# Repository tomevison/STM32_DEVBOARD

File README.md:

# STM32_DEVBOARD
Development board for STM32 microcontroller

Board features a STM32F401RCT6 MCU with a number of peripherals.
- Temperature Humidity Pressure Sensor (Bosch BME280)
- Triple Axis Accelerometer (ST LIS2DW12)
- Tactile Button
- User LED
- USB-C COM Port
- 4-30 VDC input range

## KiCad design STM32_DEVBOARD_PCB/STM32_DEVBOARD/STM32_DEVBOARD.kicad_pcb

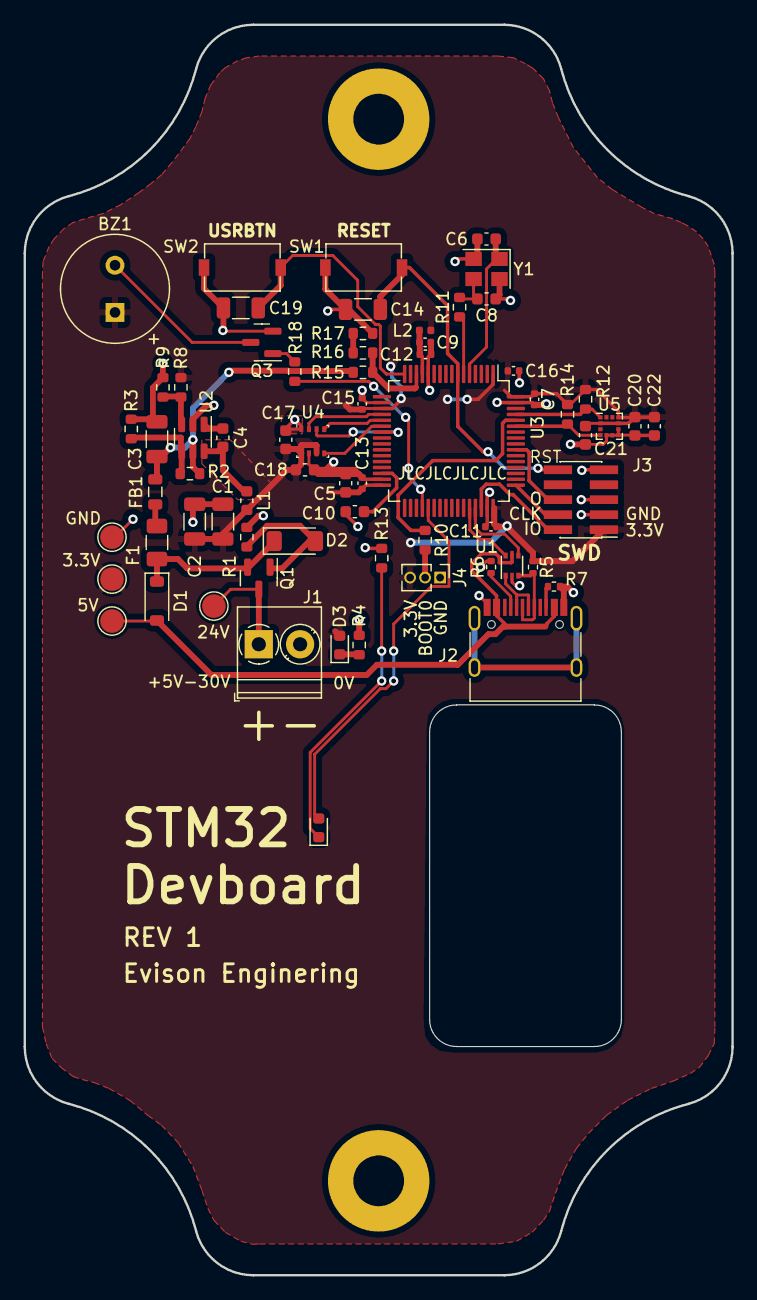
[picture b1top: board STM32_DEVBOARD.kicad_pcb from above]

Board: 2 copper layers, 60.0 x 106.0 mm, 69 parts (0 on the bottom side), 44 nets.

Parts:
BZ1: Buzzer; MagneticBuzzer_CUI_CST-931RP-A
C1, C2, C3: 10u; C_1206_3216Metric
C4: 10n; C_0603_1608Metric
C5, C10: 4u7; C_0603_1608Metric
C6, C8: 10p; C_0603_1608Metric
C7, C11, C13, C15, C16: 100n; C_0402_1005Metric
C9: 1u; C_0402_1005Metric
C12: 10n; C_0402_1005Metric
C14, C19: 0u1; C_1206_3216Metric
C17, C18, C20, C21: 100n; C_0603_1608Metric
C22: 10u; C_0603_1608Metric
D1: B5819W; D_SOD-123
D2: ZMM5V6-M; D_MiniMELF
D3, D4: GRN; LED_0603_1608Metric
F1: 250mA; Fuse_1206_3216Metric
FB1: 600 @ 600MHz; L_0805_2012Metric
H1, H2: MountingHole; MountingHole_4.3mm_M4_Pad
J1: Screw_Terminal_01x02; TerminalBlock_Phoenix_PT-1,5-2-3.5-H_1x02_P3.50mm_Horizontal
J2: USB_C_Receptacle_USB2.0; USB_C_Receptacle_HRO_TYPE-C-31-M-12
J3: SWD; PinHeader_2x05_P1.27mm_Vertical_SMD
J4: Conn_01x03_Pin; PinHeader_1x03_P1.27mm_Vertical
L1: 4.7u; L_0603_1608Metric
L2: 39n; L_0402_1005Metric
Q1: AO3401A; SOT-23
Q3: MMBT3904; SOT-23
R1, R2: 100k; R_0603_1608Metric
R3: 68k; R_0603_1608Metric
R4, R11, R13: R47; R_0603_1608Metric
R5: 1k5; R_0402_1005Metric
R6, R7: 5k1; R_0402_1005Metric
R8: 30k; R_0603_1608Metric
R9, R10, R12, R14, R17: 10k; R_0603_1608Metric
R15: 220k; R_0603_1608Metric
R16: 22k; R_0603_1608Metric
R18: 1k; R_0603_1608Metric
SW1: BTN_RSET; SW_Tactile_SPST_NO_Straight_CK_PTS636-SK25J-SMTR-LFS
SW2: BTN1; SW_Tactile_SPST_NO_Straight_CK_PTS636-SK25J-SMTR-LFS
TP1: GND; TestPoint_Pad_D2.0mm
TP2: 3.3V; TestPoint_Pad_D2.0mm
TP3: 5V; TestPoint_Pad_D2.0mm
TP4: 24V; TestPoint_Pad_D2.0mm
U1: USBLC6-2P6; SOT-666
U2: TPMP2359DJ; SOT-23-6
U3: STM32F401RCTx; LQFP-64_10x10mm_P0.5mm
U4: BME280; Bosch_LGA-8_2.5x2.5mm_P0.65mm_ClockwisePinNumbering
U5: LIS2DW12; LGA-12_2x2mm_P0.5mm
Y1: 16MHz; Crystal_SMD_3225-4Pin_3.2x2.5mm

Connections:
+3.3V: BZ1.1 (-), C1.1, C2.1, C5.1, C7.1, C11.1, C13.1, C15.1, C16.1, C17.1, C18.1, C20.1, C21.1, C22.1, D3.2 (A), J3.1, J4.3, L1.2, L2.1, R5.1, R8.1, R12.1, R14.1, TP2.1, U3.1 (VBAT), U3.19 (VDD), U3.32 (VDD), U3.48 (VDD), U3.64 (VDD), U4.6 (VDDIO), U4.8 (VDD), U5.2 (~CS), U5.9 (Vdd), U5.10 (Vdd_IO)
+3.3VA: C9.1, C12.1, L2.2, U3.13 (VREF+)
+5V: D1.2 (A), J2.A4 (VBUS), J2.A9 (VBUS), J2.B4 (VBUS), J2.B9 (VBUS), TP3.1, U1.5 (VBUS)
+24V: J1.1, Q1.3 (D), TP4.1
BOOT0: R10.2, U3.60 (BOOT0)
BTN1: C19.1, SW2.2, U3.16 (PA2)
BUCK_BST: C4.2, U2.1 (BST)
BUCK_EN: R2.2, R3.1, U2.4 (EN)
BUCK_FB: R8.2, R9.1, U2.3 (FB)
BUCK_IN: C3.1, FB1.2, R2.1, R15.2, U2.5 (IN)
BUCK_SW: C4.1, L1.1, U2.6 (SW)
BUZZ: R18.2, U3.36 (PB15)
GND: C1.2, C2.2, C3.2, C5.2, C6.2, C7.2, C8.2, C9.2, C10.2, C11.2, C12.2, C13.2, C14.2, C15.2, C16.2, C17.2, C18.2, C19.2, C20.2, C21.2, C22.2, J1.2, J2.A1 (GND), J2.A12 (GND), J2.B1 (GND), J2.B12 (GND), J3.3, J3.5, J3.9, J4.1, Q3.2 (E), R1.2, R3.2, R4.1, R6.2, R7.2, R9.2, R13.1, R17.1, SW1.1, SW2.1, TP1.1, U1.2 (GND), U2.2 (GND), U3.12 (VSSA), U3.18 (VSS), U3.31 (VSS), U3.47 (VSS), U3.63 (VSS), U4.1 (GND), U4.7 (GND), U5.5 (RES), U5.6 (GND), U5.7 (GND), U5.8 (GND), Y1.2, Y1.4
I2C1_SCL: R12.2, U3.61 (PB8), U5.1 (SCL/SPC)
I2C1_SDA: R14.2, U3.59 (PB7), U5.4 (SDA/SDI)
LED: D4.2 (A), U3.37 (PC6)
NRST: C14.1, J3.10, SW1.2, U3.7 (NRST)
unnamed: BZ1.2 (+), Q3.3 (C)
unnamed: C8.1, R11.2, Y1.3
unnamed: D1.1 (K), D2.1 (K), F1.2, Q1.2 (S)
unnamed: D2.2 (A), Q1.1 (G), R1.1
unnamed: D3.1 (K), R4.2
unnamed: D4.1 (K), R13.2
unnamed: F1.1, FB1.1
unnamed: J4.2, R10.1
unnamed: Q3.1 (B), R18.1
unnamed: R16.1, R17.2
unnamed: C10.1, U3.30 (VCAP1)
RCC_OSC_IN: C6.1, U3.5 (PH0), Y1.1
RCC_OSC_OUT: R11.1, U3.6 (PH1)
SPI1_CSB: U3.20 (PA4), U4.2 (CSB)
SPI1_MISO: U3.22 (PA6), U4.5 (SDO)
SPI1_MOSI: U3.23 (PA7), U4.3 (SDI)
SPI1_SCK: U3.21 (PA5), U4.4 (SCK)
SWCLK: J3.4, U3.49 (PA14)
SWDIO: J3.2, U3.46 (PA13)
SWO: J3.6, U3.55 (PB3)
USB_CONN_CC1: J2.A5 (CC1), R6.1
USB_CONN_CC2: J2.B5 (CC2), R7.1
USB_CONN_D+: J2.A6 (D+), J2.B6 (D+), R5.2, U1.3 (I/O2)
USB_CONN_D-: J2.A7 (D-), J2.B7 (D-), U1.1 (I/O1)
USB_OTG_FS_DN: U1.6 (I/O1), U3.44 (PA11)
USB_OTG_FS_DP: U1.4 (I/O2), U3.45 (PA12)
VMEAS: R15.1, R16.2, U3.14 (PA0)

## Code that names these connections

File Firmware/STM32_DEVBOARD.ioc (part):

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Mcu.Name=STM32F401R(B-C)Tx
Mcu.Package=LQFP64
Mcu.UserName=STM32F401RCTx
PA0-WKUP.GPIOParameters=GPIO_Label
PA0-WKUP.GPIO_Label=VMEAS
PA0-WKUP.Signal=ADCx_IN0
PA11.Mode=Device_Only
PA11.Signal=USB_OTG_FS_DM
PA12.Mode=Device_Only
PA12.Signal=USB_OTG_FS_DP
PA13.Mode=Trace_Asynchronous_SW
PA13.Signal=SYS_JTMS-SWDIO
PA14.Mode=Trace_Asynchronous_SW
PA14.Signal=SYS_JTCK-SWCLK
PA2.GPIOParameters=GPIO_PuPd,GPIO_Label
PA2.GPIO_Label=BTN1
PA2.GPIO_PuPd=GPIO_PULLUP
PA2.Signal=GPIO_Input
PA4.GPIOParameters=GPIO_Label
PA4.GPIO_Label=SPI1_CSB
PA4.Signal=GPIO_Output
PA5.Mode=Full_Duplex_Master
PA5.Signal=SPI1_SCK
PA6.Mode=Full_Duplex_Master
PA6.Signal=SPI1_MISO
PA7.Mode=Full_Duplex_Master
PA7.Signal=SPI1_MOSI
PB15.Mode=PWM Generation3 CH3N
PB15.Signal=TIM1_CH3N
PB3.Mode=Trace_Asynchronous_SW
PB3.Signal=SYS_JTDO-SWO
PB7.Mode=I2C
PB7.Signal=I2C1_SDA
PB8.Mode=I2C
PB8.Signal=I2C1_SCL
PC6.GPIOParameters=GPIO_Label
PC6.GPIO_Label=LED
PC6.Signal=GPIO_Output
PH0\ -\ OSC_IN.Mode=HSE-External-Oscillator
PH0\ -\ OSC_IN.Signal=RCC_OSC_IN
PH1\ -\ OSC_OUT.Mode=HSE-External-Oscillator
PH1\ -\ OSC_OUT.Signal=RCC_OSC_OUT
RCC.HSE_VALUE=16000000
RCC.SYSCLKFreq_VALUE=16000000
RCC.SYSCLKSource=RCC_SYSCLKSOURCE_HSE
board=custom

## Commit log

2023-05-01 Init
2023-05-02 Update symbols and check USB
2023-05-16 Added USB C connector and tidy up traces.
2023-05-17 Testing gitignore
2023-05-17 Added images and more tidy of PCB
2023-05-21 Update README.md
    Added image
2023-05-21 Added images of render
2023-05-21 Added images
2023-05-21 Update README.md
    update extension
2023-05-21 Upgrade picture quality
2023-05-22 Updates to board and start to populate BOM
2023-05-23 Added PCB render
2023-05-23 Updated render location
2023-05-23 Add pdf schematic
2023-05-23 Add plot of PCB
2023-05-24 Remove files
2023-05-24 Test
2023-05-24 will this work
2023-05-24 i think its working
2023-06-07 updated firmware examples
2023-06-18 Updated firmware
